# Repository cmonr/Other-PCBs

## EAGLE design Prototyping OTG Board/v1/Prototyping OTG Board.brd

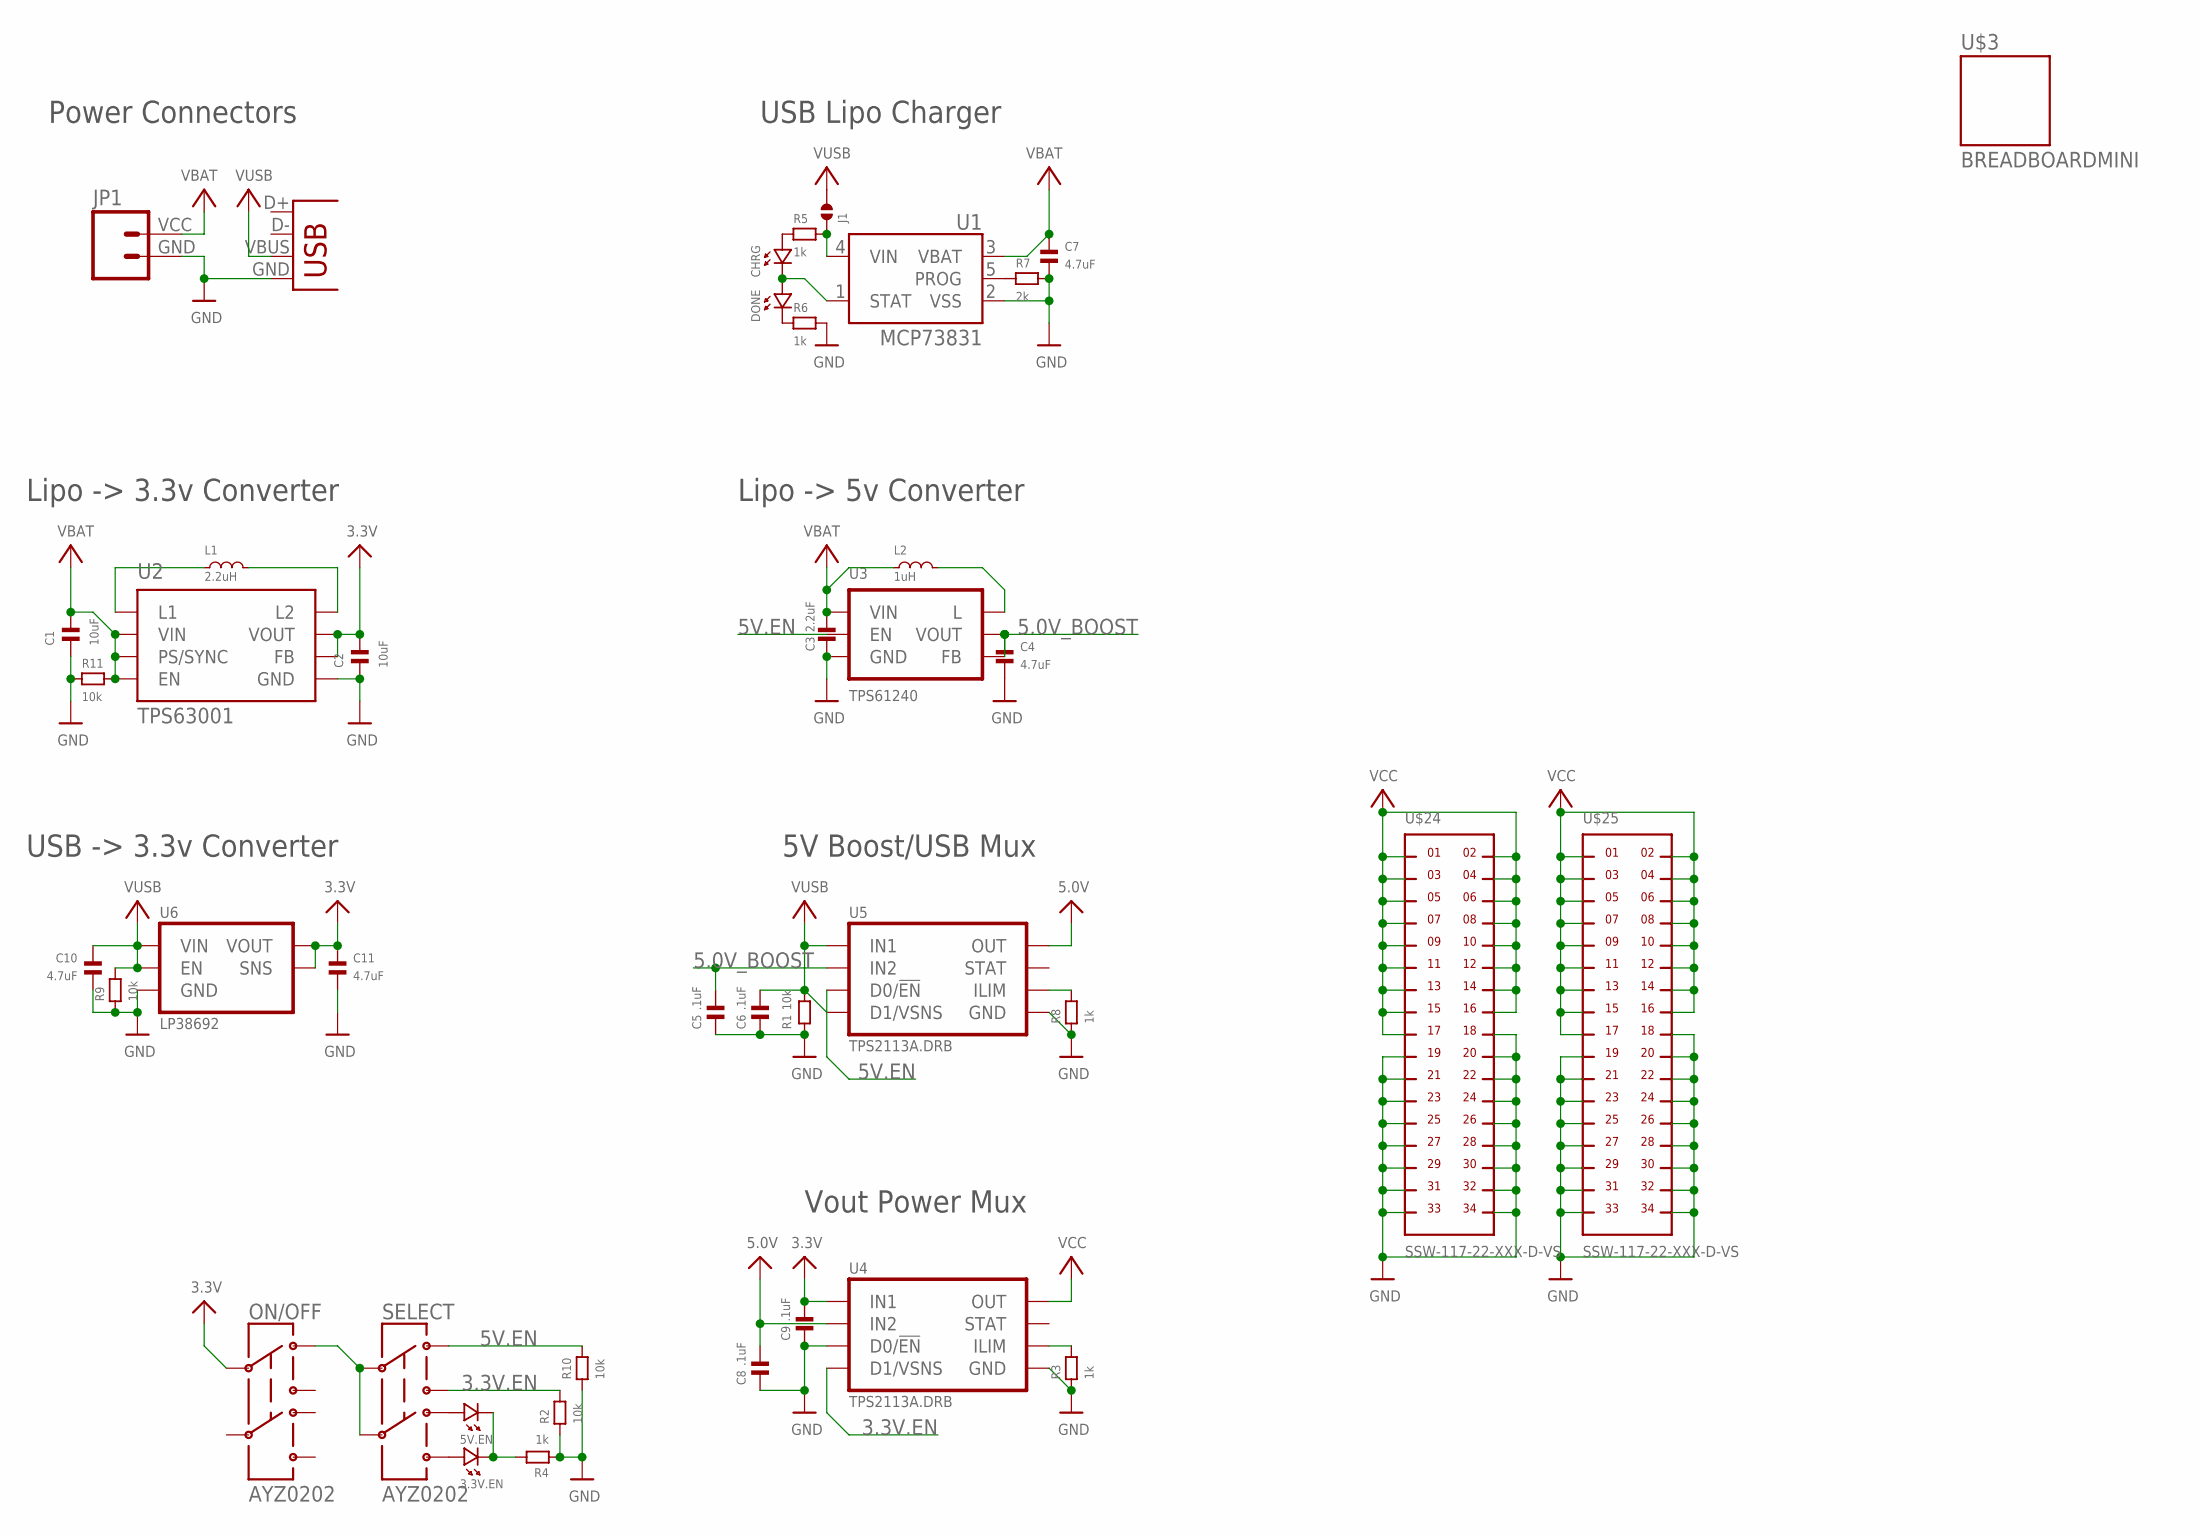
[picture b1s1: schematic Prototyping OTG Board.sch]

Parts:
3.3V.EN, 5V.EN: LED.0603; 0603.LED
C1, C2: 10uF; 0603
C3: 2.2uF; 0603
C4, C7, C10, C11: 4.7uF; 0603
C5, C6, C8, C9: .1uF; 0603
CHRG: LED.0603; 0603.LED
DONE: LED.0603; 0603.LED
J1: SOLDERJUMPER.2.LRG.PASTE; 2.LRG.PASTE
JP1: M024UCON-15767; JST-2-SMD-VERT
L1: 2.2uH; LQH3NP_M0
L2: 1uH; 0806.(2016)
ON/OFF: AYZ0202
R1, R2, R9, R10, R11: 10k; 0603
R3, R4, R5, R6, R8: 1k; 0603
R7: 2k; 0603
SELECT: AYZ0202
U1: MCP73831; SOT23-5
U2: TPS63001; DRC-S-PVSON-N10
U3: TPS61240; DRV
U4, U5: TPS2113A.DRB; DRB-S-PVSON-N8
U6: LP38692; LLP6
U$3: BREADBOARDMINI; BREADBOARD-MINI
U$24, U$25: SSW-117-22-XXX-D-VS
X1: USBSMD; USB-MINIB

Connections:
3.3V: C2.2, C9.2, C11.2, ON/OFF.2, U2.1 (VOUT), U2.10 (FB), U4.8 (IN1), U6.4 (VOUT), U6.5 (SNS)
3.3V.EN: R2.2, SELECT.1 (3), U4.3 (D1/VSNS)
5.0V: C8.2, U4.6 (IN2), U5.7 (OUT)
5.0V_BOOST: C4.2, C5.2, U3.2 (VOUT), U3.3 (FB), U5.6 (IN2)
5V.EN: R10.2, SELECT.3 (1), U3.4 (EN), U5.2 (D0/!EN)
GND: C1.1, C2.1, C3.1, C4.1, C5.1, C6.1, C7.1, C8.1, C9.1, C10.1, C11.1, JP1.GND (1), R1.1, R2.1, R3.1, R4.1, R6.2, R7.2, R8.1, R9.1, R10.1, R11.1, U1.2 (VSS), U2.3 (GND), U2.9 (GND), U2.TH (GND), U2.TH@1 (GND), U2.TH@2 (GND), U3.1 (GND), U3.PAD (GND), U4.2 (D0/!EN), U4.5 (GND), U4.TH (GND), U4.TH@1 (GND), U4.TH@2 (GND), U5.5 (GND), U5.TH (GND), U5.TH@1 (GND), U5.TH@2 (GND), U6.2 (GND), U6.PAD (GND), U$24.18, U$24.19, U$24.20, U$24.21, U$24.22, U$24.23, U$24.24, U$24.25, U$24.26, U$24.27, U$24.28, U$24.29, U$24.30, U$24.31, U$24.32, U$24.33, U$24.34, U$25.18, U$25.19, U$25.20, U$25.21, U$25.22, U$25.23, U$25.24, U$25.25, U$25.26, U$25.27, U$25.28, U$25.29, U$25.30, U$25.31, U$25.32, U$25.33, U$25.34, X1.GND
unnamed: R7.1, U1.5 (PROG)
unnamed: 5V.EN.P$1 (1), SELECT.6 (4)
unnamed: L1.1, U2.4 (L1)
unnamed: DONE.P$2 (2), R6.1
unnamed: CHRG.P$1 (1), R5.1
unnamed: CHRG.P$2 (2), DONE.P$1 (1), U1.1 (STAT)
unnamed: J1.1, R5.2, U1.4 (VIN)
unnamed: 3.3V.EN.P$1 (1), SELECT.4 (6)
unnamed: R3.2, U4.4 (ILIM)
unnamed: L1.2, U2.2 (L2)
unnamed: R8.2, U5.4 (ILIM)
unnamed: ON/OFF.3 (1), SELECT.2, SELECT.5
unnamed: 3.3V.EN.P$2 (2), 5V.EN.P$2 (2), R4.2
unnamed: L2.2, U3.5 (L)
VBAT: C1.2, C3.2, C7.2, JP1.VCC (2), L2.1, R11.2, U1.3 (VBAT), U2.5 (VIN), U2.6 (EN), U2.7 (PS/SYNC), U2.8 (VIN), U3.6 (VIN)
VCC: U4.7 (OUT), U$24.1, U$24.2, U$24.3, U$24.4, U$24.5, U$24.6, U$24.7, U$24.8, U$24.9, U$24.10, U$24.11, U$24.12, U$24.13, U$24.14, U$24.15, U$24.16, U$24.17, U$25.1, U$25.2, U$25.3, U$25.4, U$25.5, U$25.6, U$25.7, U$25.8, U$25.9, U$25.10, U$25.11, U$25.12, U$25.13, U$25.14, U$25.15, U$25.16, U$25.17
VDD: C6.2, C10.2, J1.2, R1.2, R9.2, U5.3 (D1/VSNS), U5.8 (IN1), U6.1 (VIN), U6.3 (EN), U6.6 (VIN), X1.VBUS

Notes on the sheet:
USB Lipo Charger
Lipo -> 3.3v Converter
Lipo -> 5v Converter
Power Connectors
5V Boost/USB Mux
Vout Power Mux
USB -> 3.3v Converter

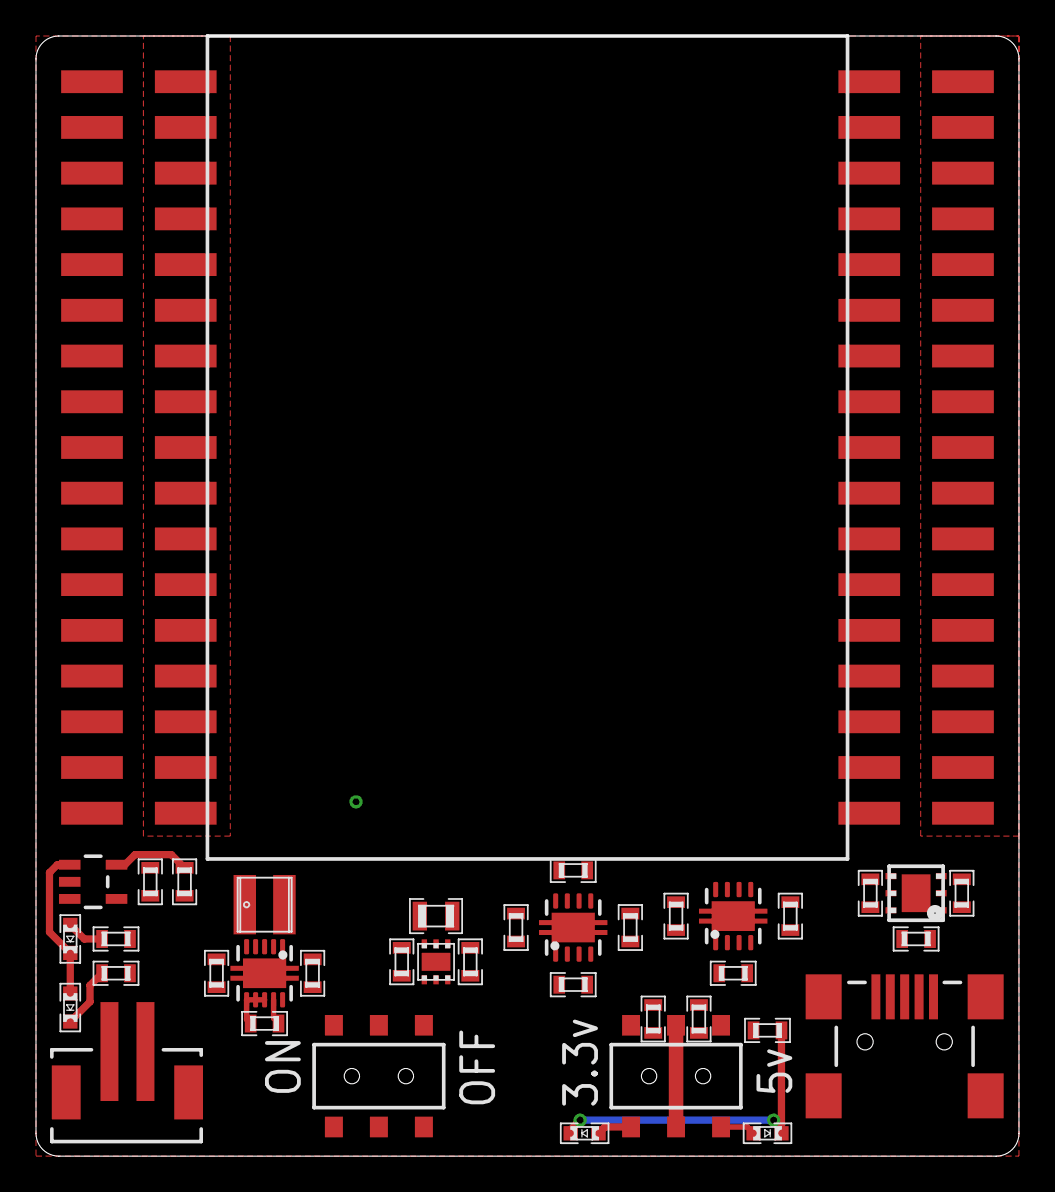
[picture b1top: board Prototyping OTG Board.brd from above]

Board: 2 copper layers, 54.6 x 62.2 mm, 42 parts (1 on the bottom side), 23 nets.

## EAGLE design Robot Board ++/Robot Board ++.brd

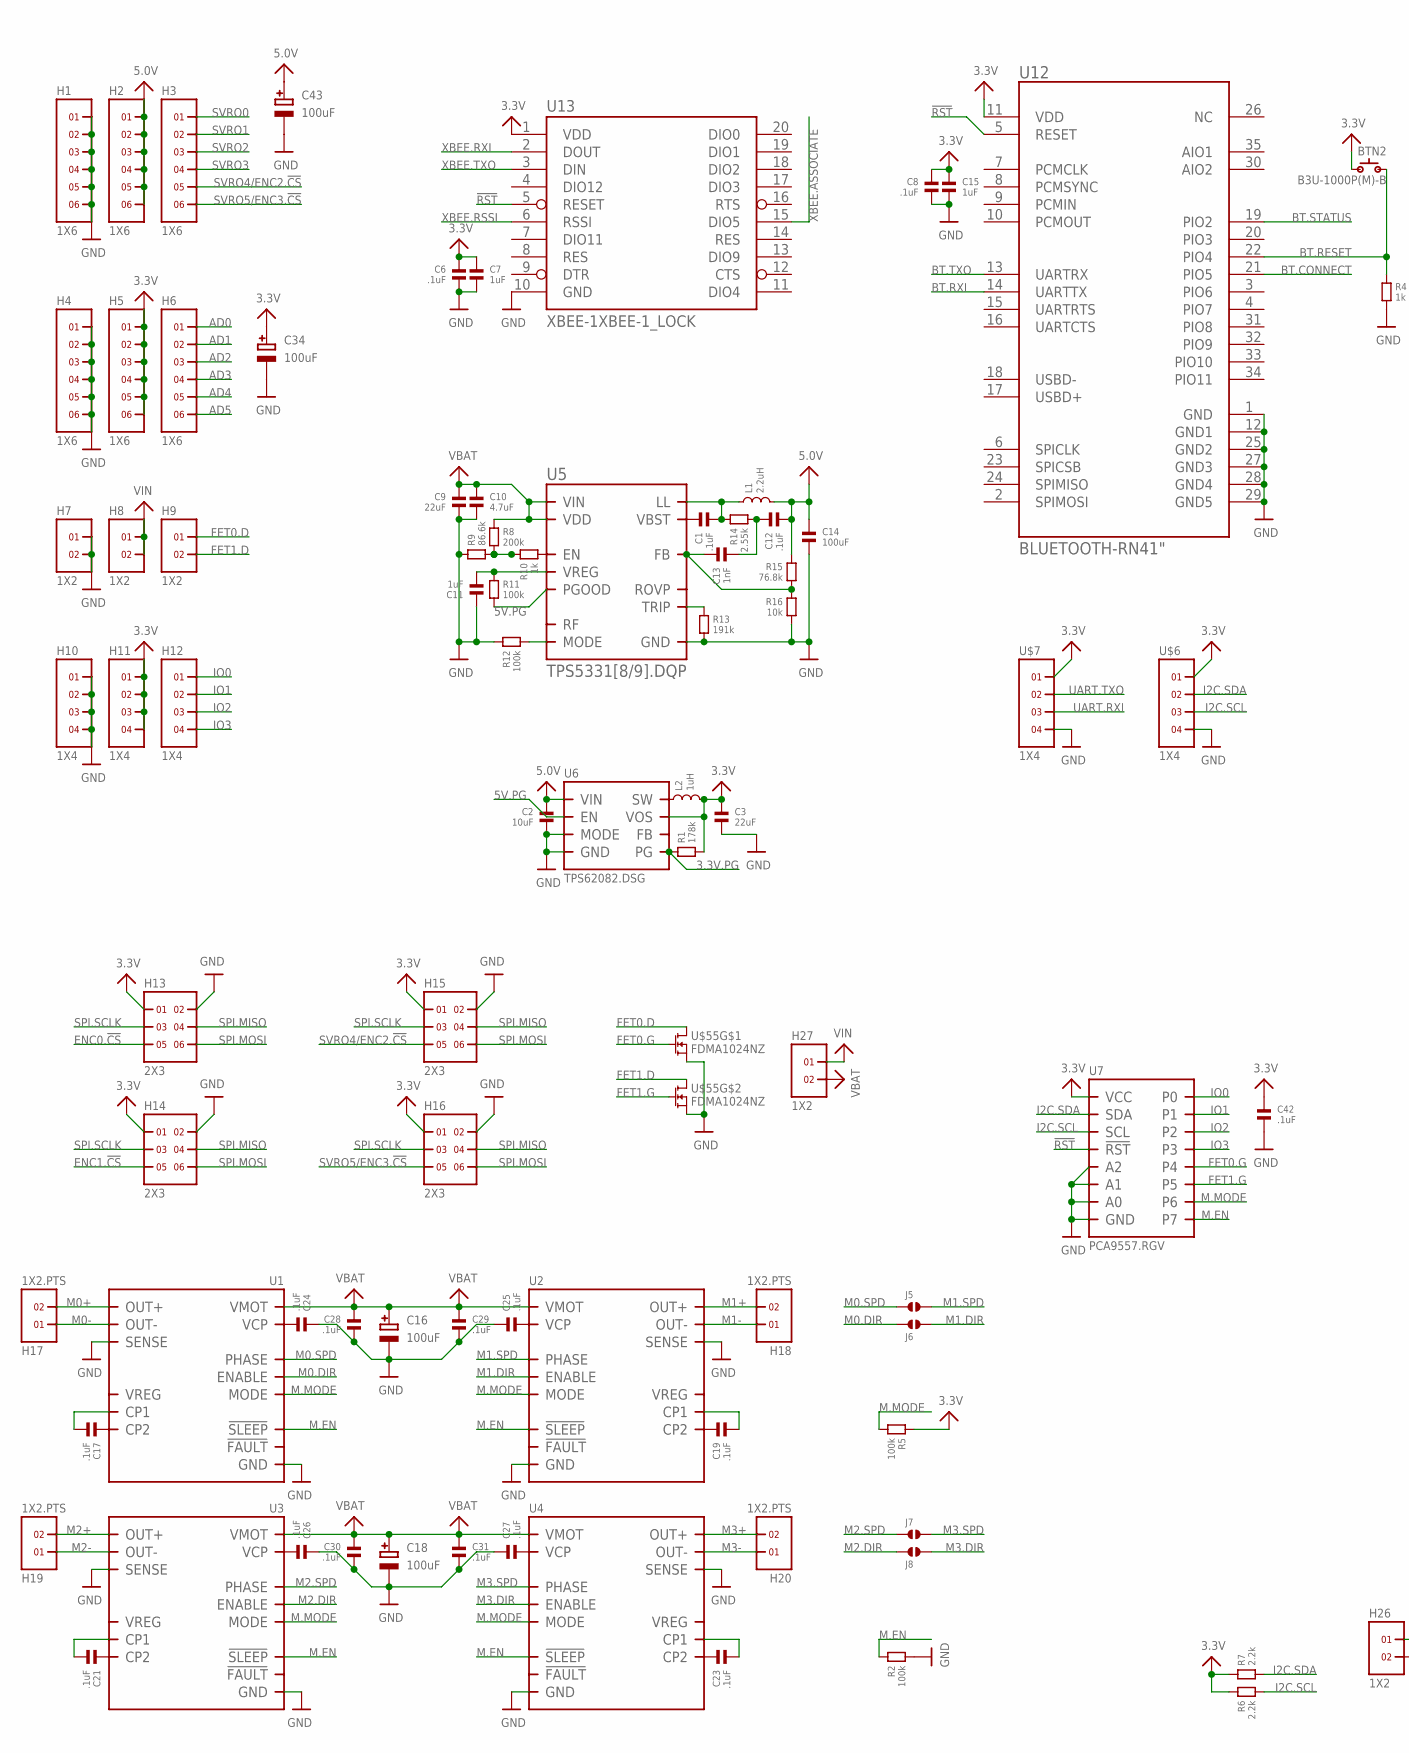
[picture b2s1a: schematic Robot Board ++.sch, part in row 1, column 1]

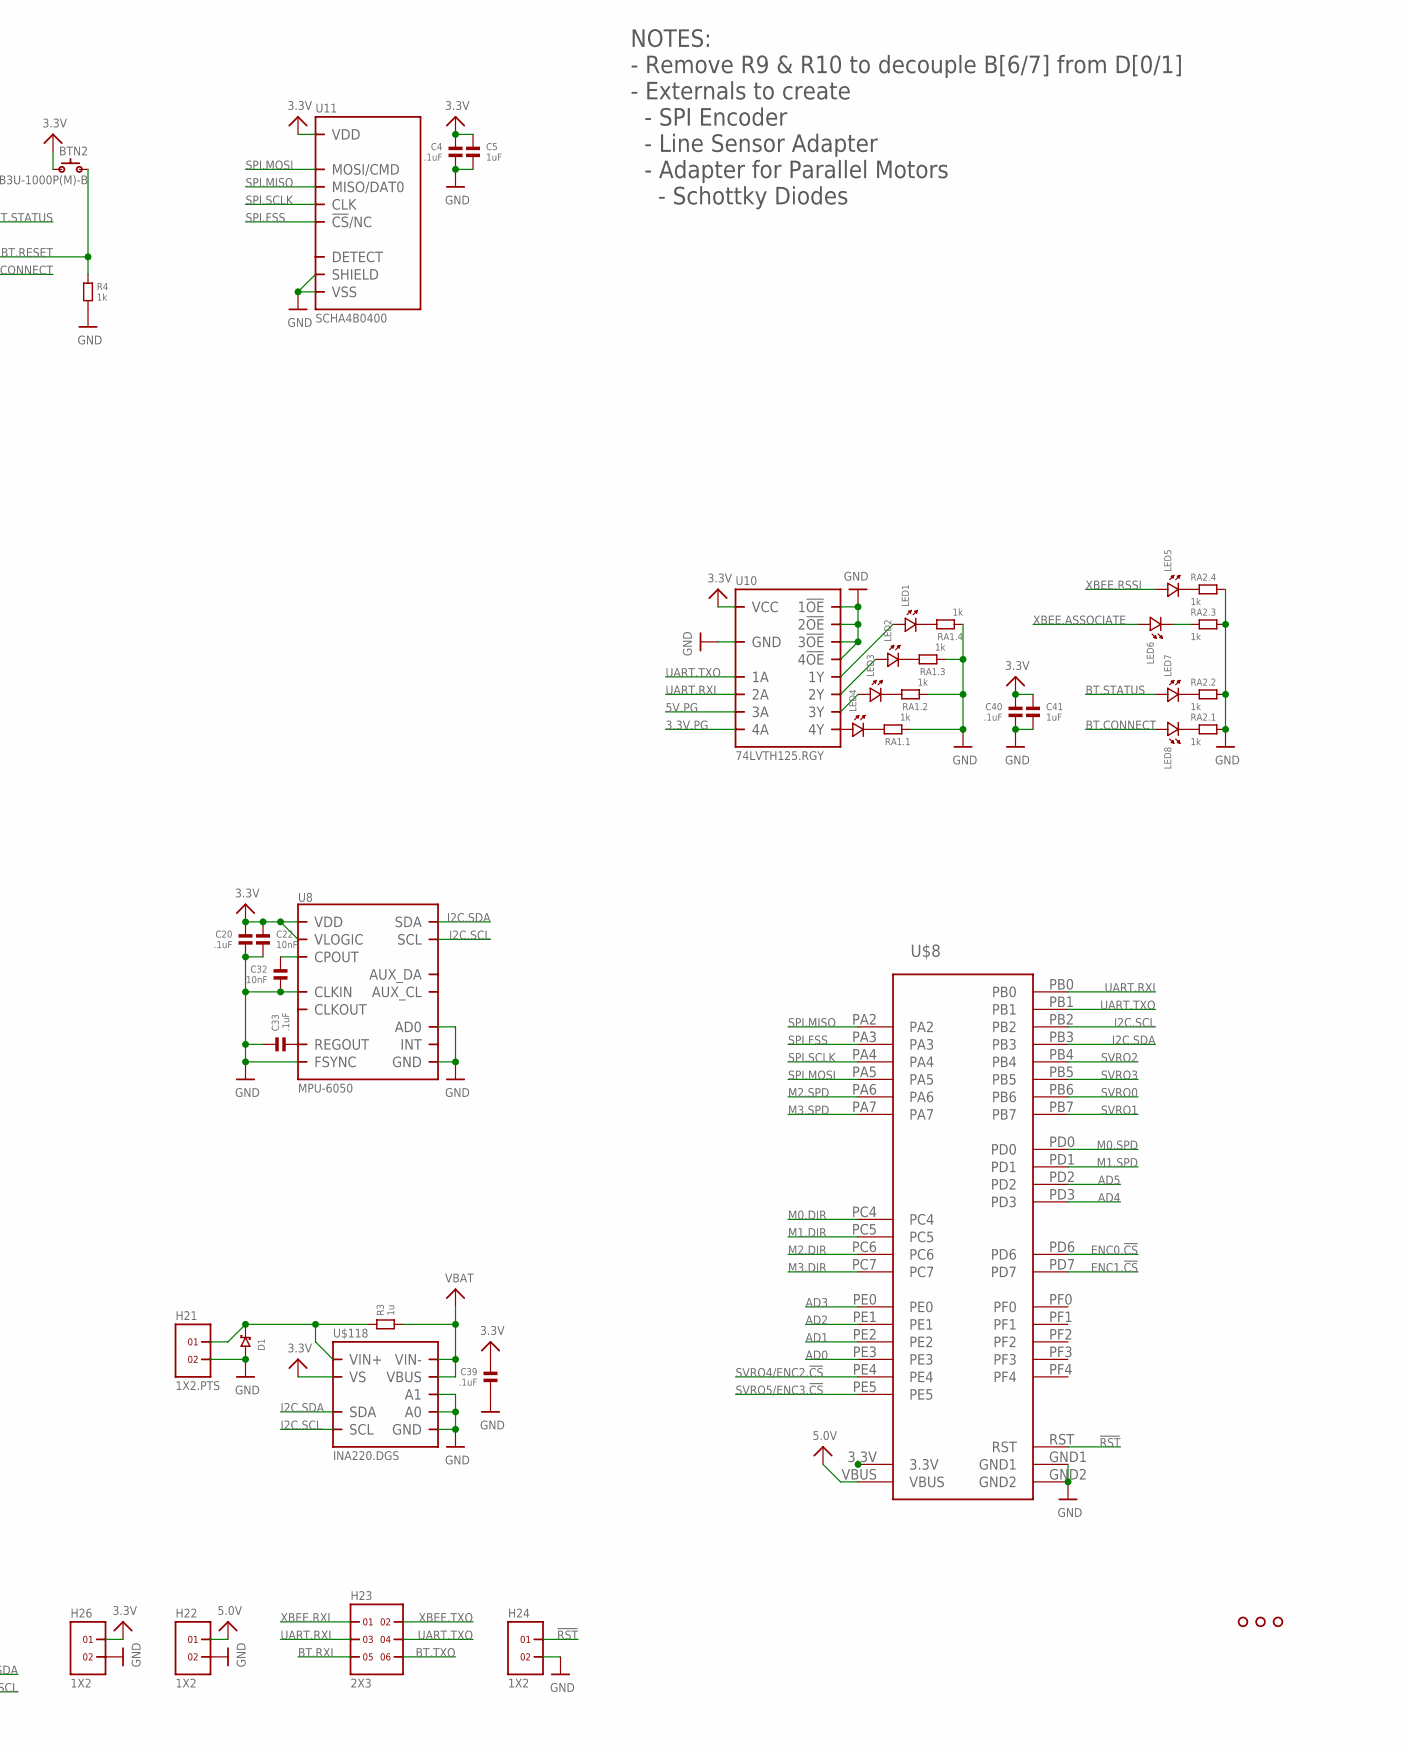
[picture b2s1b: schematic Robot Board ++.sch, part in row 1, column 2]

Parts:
BTN2: B3U-1000P(M)-B
C1, C4, C6, C8, C12, C17, C19, C20, C21, C23, C24, C25, C26, C27, C28, C29, C30, C31, C33, C39, C40, C42: .1uF; 0603
C2: 10uF; 0603
C3: 22uF; 0603
C5, C7, C11, C15, C41: 1uF; 0603
C9: 22uF; 1206
C10: 4.7uF; 0805
C13: 1nF; 0603
C14: 100uF; 1210
C16, C18, C34, C43: 100uF; PANASONIC_C
C22, C32: 10nF; 0603
D1: DIODE[SCHOTKY]-SOD123W; SOD123W
H1, H2, H3, H4, H5, H6: 1X6
H7, H8, H9, H22, H24, H26, H27: 1X2
H10, H11, H12: 1X4
H13, H14, H15, H16: 2X3; 2X3@1
H17, H18, H19, H20, H21: 1X2.PTS; PTS.PLUG
H23: 2X3
J5, J6, J7, J8: SOLDERJUMPER.2.LRG; 2.LRG
L1: 2.2uH; XAL6030
L2: 1uH; SRN3015
LED1, LED2, LED3, LED4, LED5, LED6, LED7, LED8: LED.0603; 0603.LED
R1: 178k; 0603
R2, R5, R11, R12: 100k; 0603
R3: 1u; 0612
R4, R10: 1k; 0603
R6, R7: 2.2k; 0603
R8: 200k; 0603
R9: 86.6k; 0603
R13: 191k; 0603
R14: 2.55k; 0603
R15: 76.8k; 0603
R16: 10k; 0603
RA1, RA2: 1k; 0603.4.C
U1, U2, U3, U4: DRV8800.RTY; RTY.16
U5: TPS5331[8/9].DQP; DQP.22
U6: TPS62082.DSG; DSG
U7: PCA9557.RGV; RGV.16
U8: MPU-6050; QFN.24.4X4
U10: 74LVTH125.RGY; RGY.14
U11: SCHA4B0400
U12: BLUETOOTH-RN41"; RN41
U13: XBEE-1XBEE-1_LOCK; XBEE-1_LOCK
U$3, U$4, U$11: HOLE.4MM; 4MM
U$6, U$7: 1X4
U$8: STELLARIS-LAUNCHPADSTELLARIS-LAUNCHPAD-XL; LAUNCHPAD-XL
U$55: FDMA1024NZ; MICROFET.2X2
U$118: INA220.DGS; DGS.10

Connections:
3.3V: BTN2.2, C3.1, C4.1, C5.1, C6.1, C7.1, C8.1, C15.1, C20.1, C22.1, C34.+, C39.1, C40.1, C41.1, C42.1, H5.1, H5.2, H5.3, H5.4, H5.5, H5.6, H11.1, H11.2, H11.3, H11.4, H13.1, H14.1, H15.1, H16.1, H26.1, L2.2, R1.2, R5.1, R6.1, R7.1, U6.5 (VOS), U7.14 (VCC), U8.8 (VLOGIC), U8.13 (VDD), U10.14 (VCC), U11.VDD, U12.11 (VDD), U13.1 (VDD), U$6.1, U$7.1, U$118.6 (VS)
3.3V.PG: R1.1, U6.6 (PG), U10.12 (4A)
5.0V: C2.1, C12.2, C14.1, C43.+, H2.1, H2.2, H2.3, H2.4, H2.5, H2.6, H22.1, L1.2, R15.1, U6.8 (VIN), U$8.VBUS
5V.PG: R11.2, U5.3 (PGOOD), U6.1 (EN), U10.9 (3A)
!RST: H24.1, U7.13 (!RST), U12.5 (RESET), U13.5 (RESET), U$8.RST
AD0: H6.1, U$8.PE3
AD1: H6.2, U$8.PE2
AD2: H6.3, U$8.PE1
AD3: H6.4, U$8.PE0
AD4: H6.5, U$8.PD3
AD5: H6.6, U$8.PD2
BT.CONNECT: LED8.P$1 (1), U12.21 (PIO5)
BT.RESET: BTN2.1, R4.1, U12.22 (PIO4)
BT.RXI: H23.5, U12.14 (UARTTX)
BT.STATUS: LED7.P$1 (1), U12.19 (PIO2)
BT.TXO: H23.6, U12.13 (UARTRX)
ENC0.!CS: H13.5, U$8.PD6
ENC1.!CS: H14.5, U$8.PD7
FET0.D: H9.1, U$55.6 (D), U$55.PAD@1 (D)
FET0.G: U7.9 (P4), U$55.2 (G)
FET1.D: H9.2, U$55.3 (D), U$55.PAD@2 (D)
FET1.G: U7.10 (P5), U$55.5 (G)
GND: C2.2, C3.2, C4.2, C5.2, C6.2, C7.2, C8.2, C9.2, C10.2, C11.1, C14.2, C15.2, C16.-, C18.-, C20.2, C22.2, C24.1, C25.1, C26.1, C27.1, C28.2, C29.2, C30.2, C31.2, C32.2, C33.1, C34.-, C39.2, C40.2, C41.2, C42.2, C43.-, D1.P$1 (1), H1.1, H1.2, H1.3, H1.4, H1.5, H1.6, H4.1, H4.2, H4.3, H4.4, H4.5, H4.6, H7.1, H7.2, H10.1, H10.2, H10.3, H10.4, H13.2, H14.2, H15.2, H16.2, H21.2, H22.2, H24.2, H26.2, R2.2, R4.2, R9.1, R12.1, R13.2, R16.2, RA1.1, RA1.3 (1), RA1.5 (1), RA1.7 (1), RA2.2, RA2.4 (2), RA2.6 (2), RA2.8 (2), U1.2 (GND), U1.7 (SENSE), U1.12 (GND), U1.PAD (GND), U2.2 (GND), U2.7 (SENSE), U2.12 (GND), U2.PAD (GND), U3.2 (GND), U3.7 (SENSE), U3.12 (GND), U3.PAD (GND), U4.2 (GND), U4.7 (SENSE), U4.12 (GND), U4.PAD (GND), U5.PAD (GND), U6.2 (GND), U6.3 (MODE), U6.PAD (GND), U7.1 (A0), U7.2 (A1), U7.3 (A2), U7.6 (GND), U7.PAD (GND), U8.1 (CLKIN), U8.9 (AD0), U8.11 (FSYNC), U8.18 (GND), U10.1 (1!OE), U10.4 (2!OE), U10.7 (GND), U10.10 (3!OE), U10.13 (4!OE), U10.PAD (GND), U11.GND (VSS), U11.GND@1 (VSS), U11.GND@2 (VSS), U11.SHIELD, U11.SHIELD@1 (SHIELD), U11.SHIELD@2 (SHIELD), U11.SHIELD@3 (SHIELD), U11.VSS, U12.1 (GND), U12.12 (GND1), U12.25 (GND2), U12.27 (GND3), U12.28 (GND4), U12.29 (GND5), U13.10 (GND), U$6.4, U$7.4, U$8.GND1, U$8.GND2, U$55.1 (S), U$55.4 (S), U$118.1 (A1), U$118.2 (A0), U$118.7 (GND)
I2C.SCL: R6.2, U7.15 (SCL), U8.23 (SCL), U$6.3, U$8.PB2, U$118.5 (SCL)
I2C.SDA: R7.2, U7.16 (SDA), U8.24 (SDA), U$6.2, U$8.PB3, U$118.4 (SDA)
IO0: H12.1, U7.4 (P0)
IO1: H12.2, U7.5 (P1)
IO2: H12.3, U7.7 (P2)
IO3: H12.4, U7.8 (P3)
M0+: H17.2, U1.6 (OUT+)
M0-: H17.1, U1.9 (OUT-)
M0.DIR: J6.1, U1.4 (ENABLE), U$8.PC4
M0.SPD: J5.1, U1.1 (PHASE), U$8.PD0
M1+: H18.2, U2.6 (OUT+)
M1-: H18.1, U2.9 (OUT-)
M1.DIR: J6.2, U2.4 (ENABLE), U$8.PC5
M1.SPD: J5.2, U2.1 (PHASE), U$8.PD1
M2+: H19.2, U3.6 (OUT+)
M2-: H19.1, U3.9 (OUT-)
M2.DIR: J8.1, U3.4 (ENABLE), U$8.PC6
M2.SPD: J7.1, U3.1 (PHASE), U$8.PA6
M3+: H20.2, U4.6 (OUT+)
M3-: H20.1, U4.9 (OUT-)
M3.DIR: J8.2, U4.4 (ENABLE), U$8.PC7
M3.SPD: J7.2, U4.1 (PHASE), U$8.PA7
M.EN: R2.1, U1.3 (!SLEEP), U2.3 (!SLEEP), U3.3 (!SLEEP), U4.3 (!SLEEP), U7.12 (P7)
M.MODE: R5.2, U1.16 (MODE), U2.16 (MODE), U3.16 (MODE), U4.16 (MODE), U7.11 (P6)
unnamed: C1.1, U5.4 (VBST)
unnamed: R12.2, U5.20 (MODE)
unnamed: C11.2, R11.1, U5.18 (VREG)
unnamed: R13.1, U5.21 (TRIP)
unnamed: LED1.P$1 (1), U10.3 (1Y)
unnamed: C33.2, U8.10 (REGOUT)
unnamed: R10.2, U5.2 (EN)
unnamed: LED8.P$2 (2), RA2.1
unnamed: C13.1, R15.2, R16.1, U5.1 (FB)
unnamed: R8.2, R9.2, R10.1
unnamed: L2.1, U6.7 (SW)
unnamed: C17.1, U1.11 (CP2)
unnamed: C12.1, C13.2, R14.2
unnamed: C1.2, L1.1, R14.1, U5.6 (LL), U5.7 (LL), U5.8 (LL), U5.9 (LL), U5.10 (LL), U5.11 (LL)
unnamed: C24.2, U1.13 (VCP)
unnamed: C25.2, U2.13 (VCP)
unnamed: C26.2, U3.13 (VCP)
unnamed: C27.2, U4.13 (VCP)
unnamed: D1.P$2 (2), H21.1, R3.1@1 (1), R3.1@2 (1), U$118.10 (VIN+)
unnamed: C32.1, U8.20 (CPOUT)
unnamed: C19.1, U2.11 (CP2)
unnamed: C21.1, U3.11 (CP2)
unnamed: C23.1, U4.11 (CP2)
unnamed: C21.2, U3.10 (CP1)
unnamed: C17.2, U1.10 (CP1)
unnamed: C19.2, U2.10 (CP1)
unnamed: C23.2, U4.10 (CP1)
unnamed: LED2.P$1 (1), U10.6 (2Y)
unnamed: LED4.P$1 (1), U10.11 (4Y)
unnamed: LED7.P$2 (2), RA2.3 (1)
unnamed: LED6.P$2 (2), RA2.5 (1)
unnamed: LED5.P$2 (2), RA2.7 (1)
unnamed: LED4.P$2 (2), RA1.2
unnamed: LED3.P$1 (1), U10.8 (3Y)
unnamed: LED1.P$2 (2), RA1.8 (2)
unnamed: LED2.P$2 (2), RA1.6 (2)
unnamed: LED3.P$2 (2), RA1.4 (2)
SPI.FSS: U11.!CS!/NC/DAT3 (!CS!/NC), U$8.PA3
SPI.MISO: H13.4, H14.4, H15.4, H16.4, U11.MISO/DAT0, U$8.PA2
SPI.MOSI: H13.6, H14.6, H15.6, H16.6, U11.MOSI/CMD, U$8.PA5
SPI.SCLK: H13.3, H14.3, H15.3, H16.3, U11.CLK, U$8.PA4
SVRO0: H3.1, U$8.PB6
SVRO1: H3.2, U$8.PB7
SVRO2: H3.3, U$8.PB4
SVRO3: H3.4, U$8.PB5
SVRO4/ENC2.!CS: H3.5, H15.5, U$8.PE4
SVRO5/ENC3.!CS: H3.6, H16.5, U$8.PE5
UART.RXI: H23.3, U10.5 (2A), U$7.3, U$8.PB0
UART.TXO: H23.4, U10.2 (1A), U$7.2, U$8.PB1
VBAT: C9.1, C10.1, C16.+, C18.+, C28.1, C29.1, C30.1, C31.1, H27.2, R3.2@1 (2), R3.2@2 (2), R8.1, U1.8 (VMOT), U2.8 (VMOT), U3.8 (VMOT), U4.8 (VMOT), U5.12 (VIN), U5.13 (VIN), U5.14 (VIN), U5.15 (VIN), U5.16 (VIN), U5.17 (VIN), U5.19 (VDD), U$118.8 (VBUS), U$118.9 (VIN-)
VIN: H8.1, H8.2, H27.1
XBEE.ASSOCIATE: LED6.P$1 (1), U13.15 (DIO5)
XBEE.RSSI: LED5.P$1 (1), U13.6 (RSSI)
XBEE.RXI: H23.1, U13.2 (DOUT)
XBEE.TXO: H23.2, U13.3 (DIN)

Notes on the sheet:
NOTES: - Remove R9 & R10 to decouple B[6/7] from D[0/1] - Externals to create - SPI Encoder - Line Sensor Adapter - Adapter for Parallel Motors - Schottky Diodes

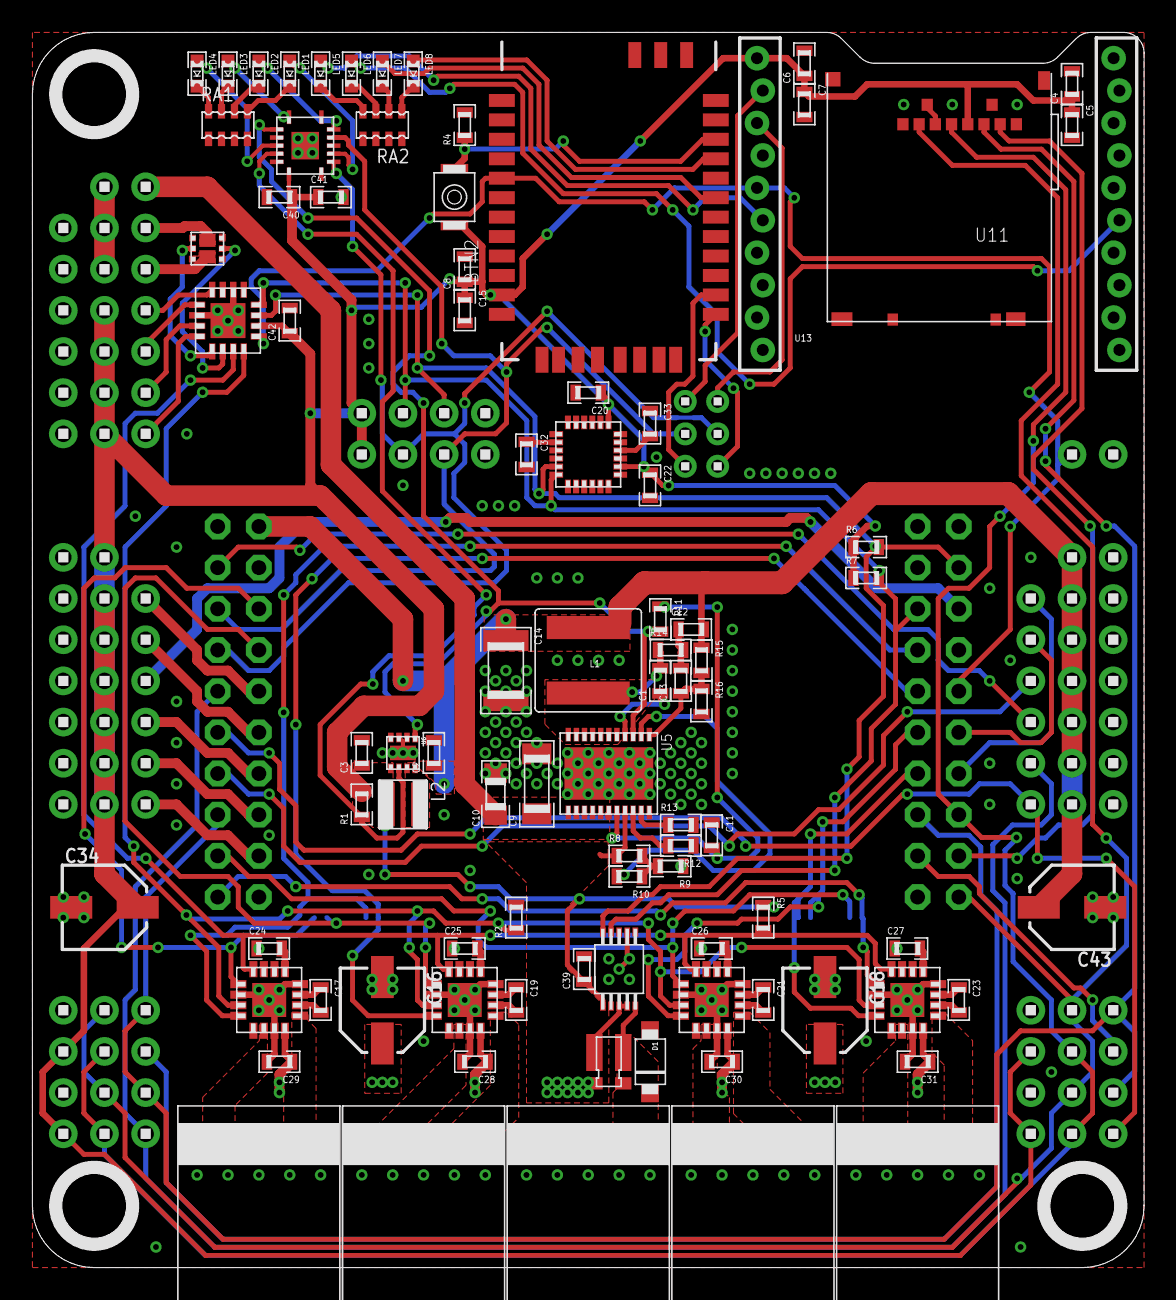
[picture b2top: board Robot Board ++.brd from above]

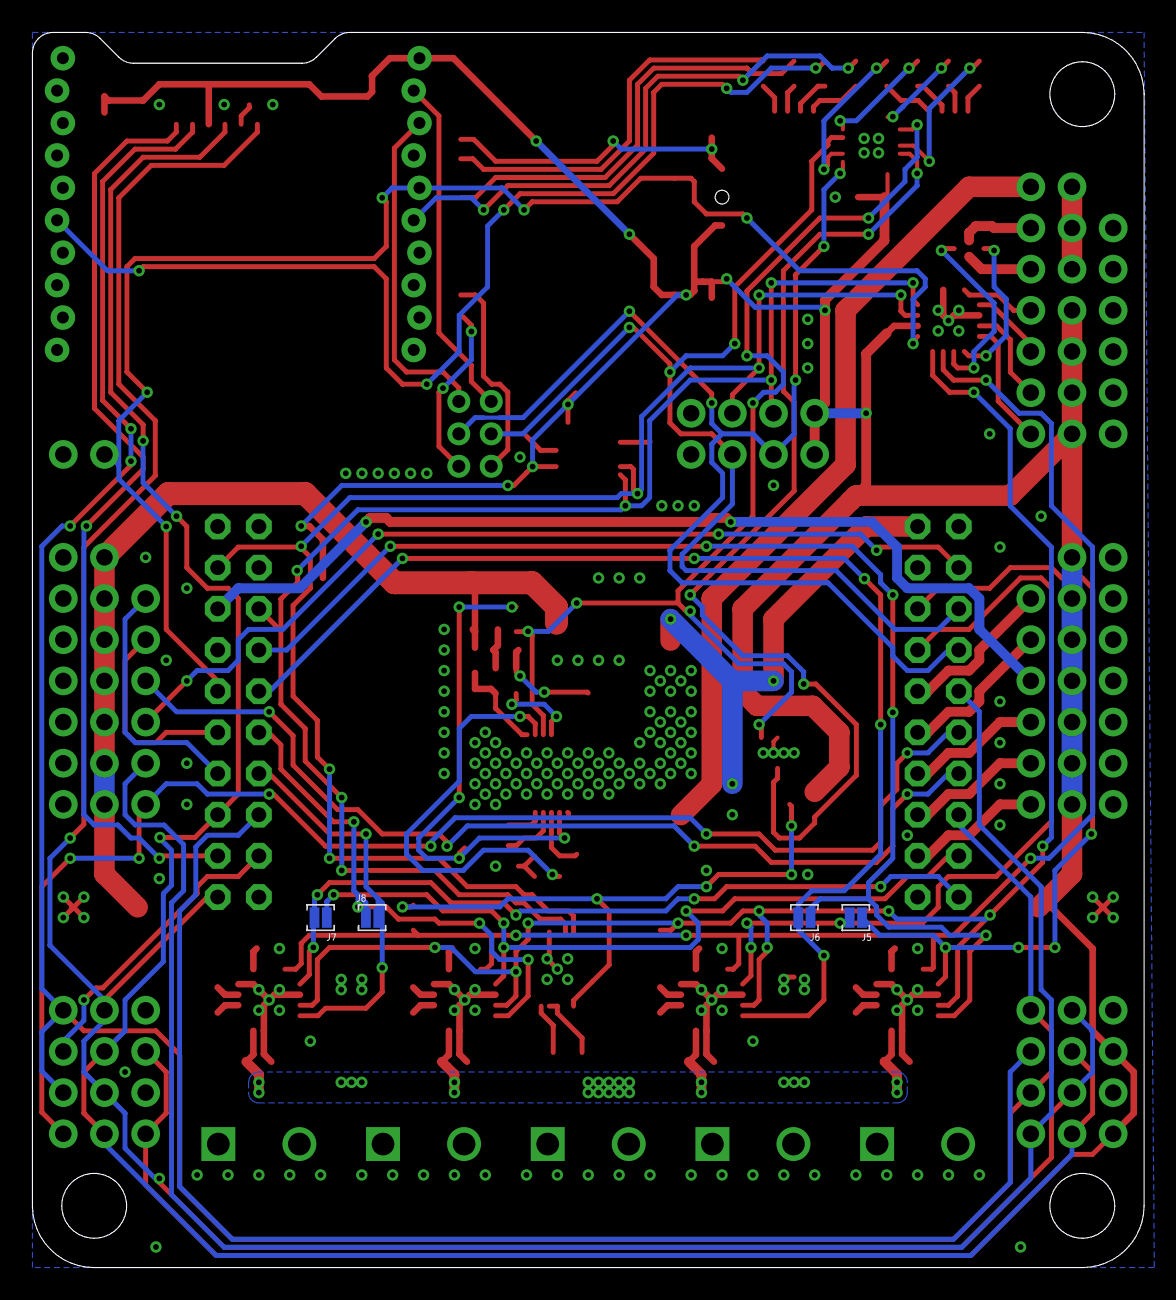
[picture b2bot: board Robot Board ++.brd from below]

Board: 2 copper layers, 68.6 x 76.2 mm, 119 parts (4 on the bottom side), 102 nets.

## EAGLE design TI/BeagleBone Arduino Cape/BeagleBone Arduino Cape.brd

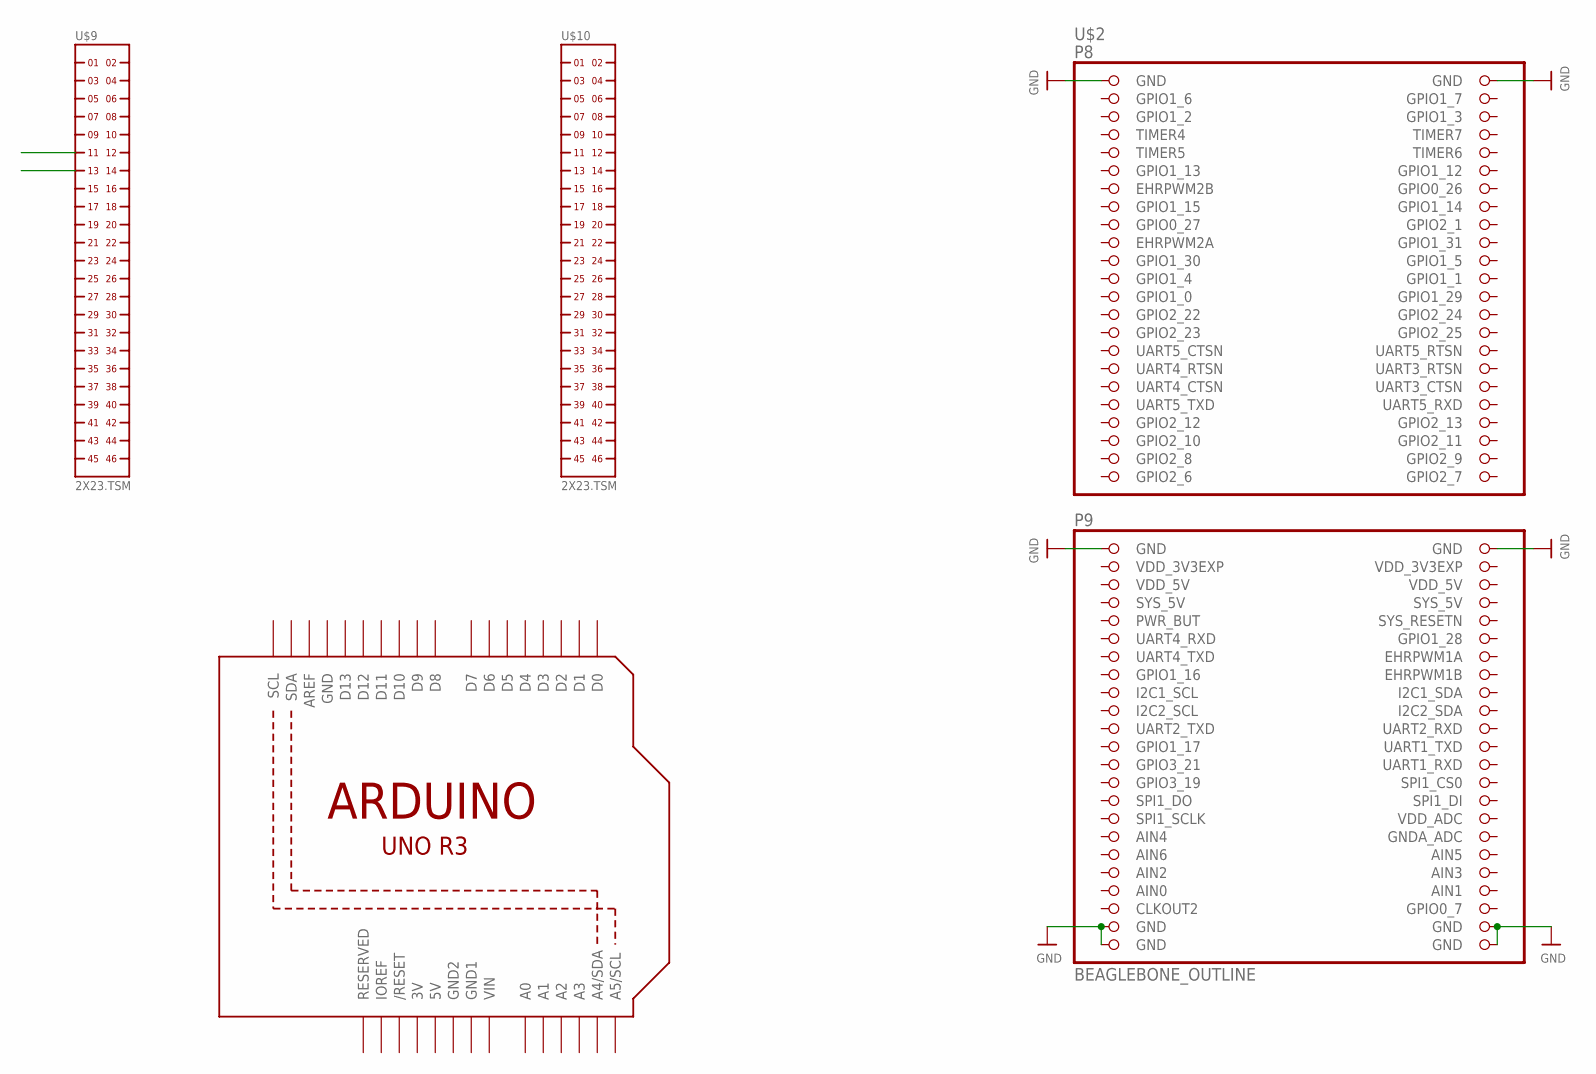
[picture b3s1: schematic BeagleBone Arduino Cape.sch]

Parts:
U1: ARDUINOR3-BPLACE
U$2: BEAGLEBONE_OUTLINE; BEAGLEBONE_SHIELD
U$9, U$10: 2X23.TSM; TSM-123-XX-XXX-DV

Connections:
3V: U1.3V
5V: U1.5V
AIN0: U$2.85 (AIN0)
GND: U1.GND, U$2.1 (GND), U$2.2 (GND), U$2.47 (GND), U$2.48 (GND), U$2.89 (GND), U$2.90 (GND), U$2.91 (GND), U$2.92 (GND)
GND1: U1.GND1
GND2: U1.GND2
SYS_5V: U$2.53 (SYS_5V)
VDD_3V3EXP: U$2.49 (VDD_3V3EXP), U$2.50 (VDD_3V3EXP)
VDD_5V: U$2.51 (VDD_5V), U$2.52 (VDD_5V)
VIN: U1.VIN

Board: 2 copper layers, 4 parts (2 on the bottom side), 3 nets, no tracks yet.

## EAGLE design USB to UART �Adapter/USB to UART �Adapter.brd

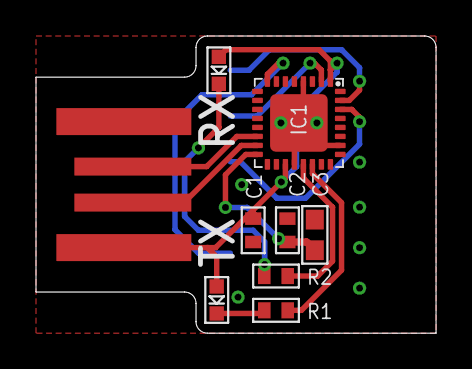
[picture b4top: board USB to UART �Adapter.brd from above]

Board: 2 copper layers, 22.2 x 16.5 mm, 10 parts (1 on the bottom side), 13 nets.

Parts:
C1, C2: .1uF; 0402
C3: 4.7uF; 0603
IC1: FT232RQ; QFN32
R1, R2: 1k; 0402
RX: CHIPLED_0603
TX: CHIPLED_0603
U$3: SMH-106-XX-X-S
X1: USBPCB; USB-A-PCB

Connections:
3.3V: C2.2, C3.2, IC1.16, U$3.3
5.0V: C1.2, IC1.1, IC1.19, RX.A, TX.A, X1.5V
!CTS: IC1.8, U$3.2
!DTR: IC1.31, U$3.6
D+: IC1.14, X1.USB_P
D-: IC1.15, X1.USB_M
GND: C1.1, C2.1, C3.1, IC1.4, IC1.17, IC1.20, IC1.24, IC1.26, IC1.EXP, U$3.1, X1.GND
unnamed: R2.1, RX.C
unnamed: IC1.22, R1.2
unnamed: R1.1, TX.C
unnamed: IC1.21, R2.2
RX: IC1.2, U$3.5
TX: IC1.30, U$3.4

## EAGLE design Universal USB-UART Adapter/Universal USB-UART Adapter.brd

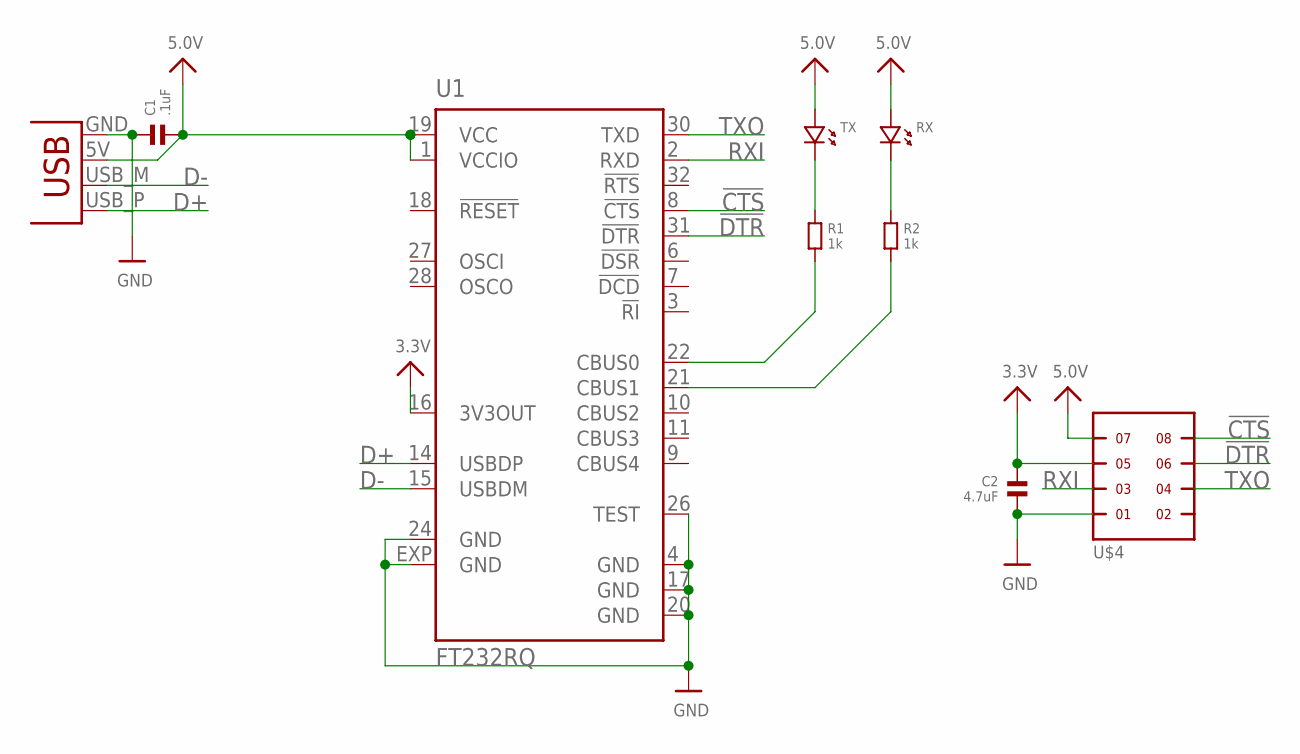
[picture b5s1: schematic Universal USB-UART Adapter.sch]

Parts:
C1: .1uF; 0603
C2: 4.7uF; 0603
R1, R2: 1k; 0603
RX: LED.0603; 0603.LED
TX: LED.0603; 0603.LED
U1: FT232RQ; QFN32
U$4: MMT-104-01-X-DH-X
X1: USBPCB; USB-A-PCB

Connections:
3.3V: C2.1, U1.16 (3V3OUT), U$4.5
5.0V: C1.2, RX.P$1 (1), TX.P$1 (1), U1.1 (VCCIO), U1.19 (VCC), U$4.7, X1.5V (VBUS)
!CTS: U1.8 (!CTS), U$4.8
!DTR: U1.31 (!DTR), U$4.6
D+: U1.14 (USBDP), X1.USB_P (D+)
D-: U1.15 (USBDM), X1.USB_M (D-)
GND: C1.1, C2.2, U1.4 (GND), U1.17 (GND), U1.20 (GND), U1.24 (GND), U1.26 (TEST), U1.EXP (GND), U$4.1, X1.GND
unnamed: R2.1, RX.P$2 (2)
unnamed: R1.2, U1.22 (CBUS0)
unnamed: R1.1, TX.P$2 (2)
unnamed: R2.2, U1.21 (CBUS1)
RXI: U1.2 (RXD), U$4.3
TXO: U1.30 (TXD), U$4.4

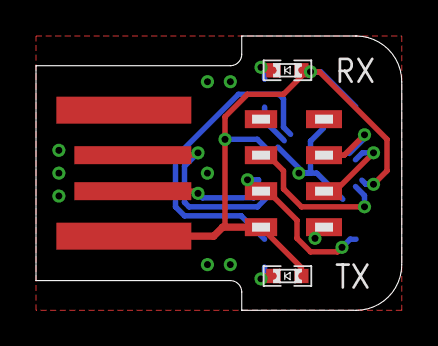
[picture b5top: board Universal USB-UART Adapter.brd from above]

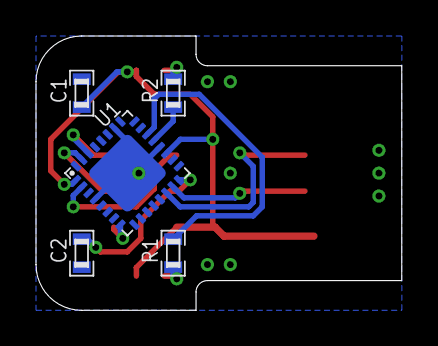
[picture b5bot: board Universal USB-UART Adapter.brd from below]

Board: 2 copper layers, 20.3 x 15.2 mm, 9 parts (5 on the bottom side), 13 nets.

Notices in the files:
parts and their libraries:
SparkFun-RF: Licensing: CC v3.0 Share-Alike You are welcome to use this library for commercial purposes.
microbuilder: This work is placed in the public domain, and may be freely used for commercial and non-commercial work with the following conditions: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
